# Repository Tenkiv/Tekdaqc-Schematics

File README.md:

# TekdaqcSchematics

pcb file for RevE and RevF are incomplete
- all digital grounds are currently unconnected
#TODO ground plane

RevE contains the files for the current Tekdaqc version

RevF is a modified version of the current Tekdaqc
- GIP15 is moved from PC14 to PH5
- GPI4 is moved from PH0 to PH3
- Digital Output connection has been modified to include a pull down resistor

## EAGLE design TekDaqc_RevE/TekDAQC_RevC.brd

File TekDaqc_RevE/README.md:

Folder contains all necessary files to open and make changes to the schematic and pcb files in KiCad

*.pro - project file

*.sch - schematic files

*.lib - contains the components used in the schematic 

*.kicad_pcb - pcb file

*.pretty - contains the files of the footprints used in the pcb file

*.kicad_mod - footprint of the components used in the pcb file

*.net - links the schematic files to the pcb files

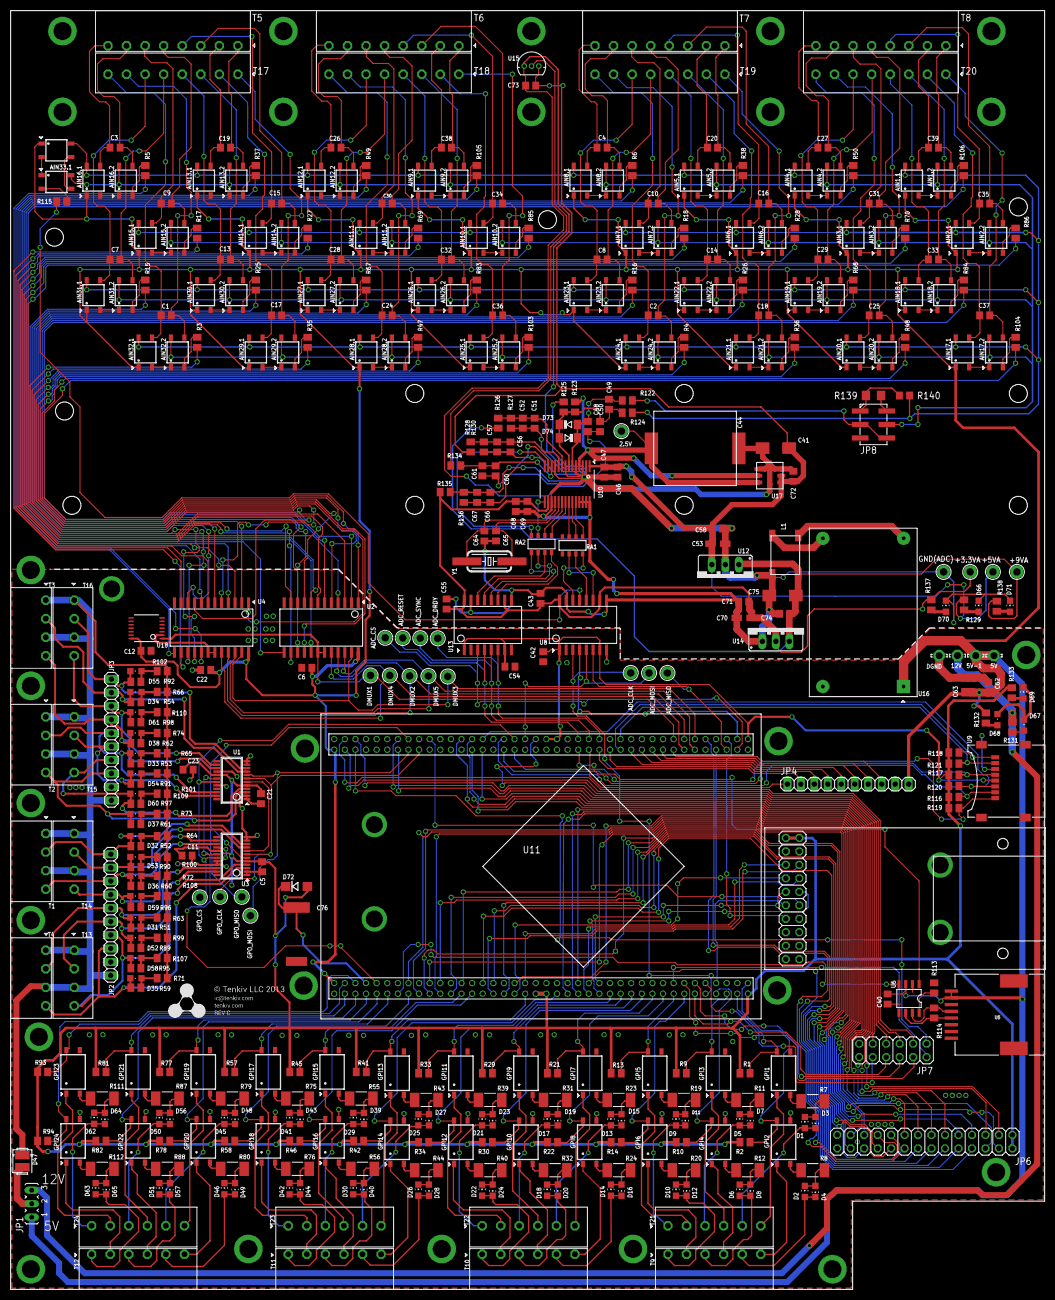
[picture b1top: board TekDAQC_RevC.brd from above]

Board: 2 copper layers, 194.9 x 241.1 mm, 458 parts (0 on the bottom side), 446 nets.

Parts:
2.5V: R; KEYSTONE_5000
5V, 5V-1, 12V: LSP13
+3.3VA, +5VA, +9VA: R; KEYSTONE_5000
ADC_CLK: Y; KEYSTONE_5000
ADC_CS: Y; KEYSTONE_5000
ADC_DRDY: Y; KEYSTONE_5000
ADC_MISO: B; KEYSTONE_5000
ADC_MOSI: W; KEYSTONE_5000
ADC_RESET: W; KEYSTONE_5000
ADC_SYNC: O; KEYSTONE_5000
AIN1.1, AIN1.2, AIN2.1, AIN2.2, AIN3.1, AIN3.2, AIN4.1, AIN4.2, AIN5.1, AIN5.2, AIN6.1, AIN6.2, AIN7.1, AIN7.2, AIN8.1, AIN8.2, AIN9.1, AIN9.2, AIN10.1, AIN10.2, AIN11.1, AIN11.2, AIN12.1, AIN12.2, AIN13.1, AIN13.2, AIN14.1, AIN14.2, AIN15.1, AIN15.2, AIN16.1, AIN16.2, AIN17.1, AIN17.2, AIN18.1, AIN18.2, AIN19.1, AIN19.2, AIN20.1, AIN20.2, AIN21.1, AIN21.2, AIN22.1, AIN22.2, AIN23.1, AIN23.2, AIN24.1, AIN24.2, AIN25.1, AIN25.2, AIN26.1, AIN26.2, AIN27.1, AIN27.2, AIN28.1, AIN28.2, AIN29.1, AIN29.2, AIN30.1, AIN30.2, AIN31.1, AIN31.2, AIN32.1, AIN32.2, AIN33.1, AIN33.2: CPC1025N; SOP4
C1, C2, C3, C4, C5, C6, C7, C8, C9, C10, C11, C12, C13, C14, C15, C16, C17, C18, C19, C20, C21, C22, C23, C24, C25, C26, C27, C28, C29, C30, C31, C32, C33, C34, C35, C36, C37, C38, C39, C40, C42, C43, C46, C49, C52, C54, C55, C57, C58, C61, C62, C67, C68, C71, C72, C73, C74: 0.1uF; C0805
C41, C75: 10uF; CT6032
C44: 4.7uF; 6054
C47, C69: 10uF; C0805
C48, C50: 0.01uF; C0805
C51, C56, C60, C66: 100pF; C0805
C53, C70: 15uF; CT3216
C63: 47uF; C1210
C64, C65: 18pF; C0805
C76: ELNA0_0.33F_CAP; COIN_CELL_CAP
D1, D2, D3, D4, D5, D6, D7, D8, D9, D10, D11, D12, D13, D14, D15, D16, D17, D18, D19, D20, D21, D22, D23, D24, D25, D26, D27, D28, D29, D30, D39, D40, D41, D42, D43, D44, D45, D46, D48, D49, D50, D51, D56, D57, D62, D63, D64, D65: R; CHIP-LED0805
D31, D32, D33, D34, D35, D36, D37, D38, D52, D53, D54, D55, D58, D59, D60, D61: B; CHIPLED_0805
D47: DIODE(DO-214AA); DO−214AA
D66: +5V; CHIP-LED0805
D67: +12V; CHIPLED_0805
D68: +5V; CHIPLED_0805
D69: MCU PWR; CHIP-LED0805
D70: +3.3V; CHIP-LED0805
D71: +9V; CHIP-LED0805
D72: CDBA120LL-G; DO214AC
D73, D74: TZMC5V1-GS08; SOD80C
DGND: LSP13
DMUX1, DMUX2, DMUX3, DMUX4, DMUX5: O; KEYSTONE_5000
DRILEGEND: DRILEGEND
GND(ADC): B; KEYSTONE_5000
GPI1, GPI2, GPI3, GPI4, GPI5, GPI6, GPI7, GPI8, GPI9, GPI10, GPI11, GPI12, GPI13, GPI14, GPI15, GPI16, GPI17, GPI18, GPI19, GPI20, GPI21, GPI22, GPI23, GPI24: 4-SMD
GPO_CLK: Y; KEYSTONE_5000
GPO_CS: Y; KEYSTONE_5000
GPO_MISO: B; KEYSTONE_5000
GPO_MOSI: W; KEYSTONE_5000
JP1: OutputSupply; JP2
JP2: Relay2; 1X10
JP3, JP4: Relay1; 1X10
JP5: ETH Header; ETH_2X10
JP6: Misc Header; 2X14
JP7: PWM Header; 2X06
JP8: 2X3PIN_SMT_HEADER; 2X3SMT_HEADER
L1: BOURNES_DR331-475BE; DR331_CHOKE
R1, R2, R9, R10, R13, R14, R21, R22, R29, R30, R33, R34, R41, R42, R45, R46, R57, R58, R77, R78, R81, R82, R93, R94, R130, R131, R135, R136: 1k; M0805
R3, R4, R5, R6, R15, R16, R17, R18, R25, R26, R27, R28, R35, R36, R37, R38, R47, R48, R49, R50, R63, R64, R65, R66, R67, R68, R69, R70, R71, R72, R73, R74, R83, R84, R85, R86, R99, R100, R101, R102, R103, R104, R105, R106, R107, R108, R109, R110, R115: 442; M0805
R7, R8, R11, R12, R19, R20, R23, R24, R31, R32, R39, R40, R43, R44, R55, R56, R75, R76, R79, R80, R87, R88, R111, R112: 330; R2010
R51, R52, R53, R54, R59, R60, R61, R62, R89, R90, R91, R92, R95, R96, R97, R98, R125: 1M; M0805
R113: 49.9k; M0805
R114: 60; M0805
R116, R117, R118, R119, R120, R121: 10K; M0805
R122, R124, R134: 301; M0805
R123: 0; M0805
R126, R138: 8k; M0805
R127, R128: 2k; M0805
R129, R132, R133, R137: 330; M0805
R139: 1M; R1206
R140: 12.7k; R0805
RA1, RA2: 744C083101JP; 5131(744SERIES)
T1, T2, T3, T4: 4POLE_PLUGIN_TERMINAL_SIDE; 4POLE_3.5MM_TERMINAL_SIDE
T5, T6, T7, T8: 8POLE_PLUGIN_TERMINAL_SIDE; 8POLE_3.5MM_TERMINAL_SIDE
T9, T10, T11, T12: 6POLE_PLUGIN_TERMINAL_SIDE; 6POLE_3.5MM_TERMINAL_SIDE
T13, T14, T15, T16: 4POLE_PLUGIN_TERMINAL_TOP; 4POLE_3.5MM_TERMINAL_TOP
T17, T18, T19, T20: 8POLE_PLUGIN_TERMINAL_TOP; 8POLE_3.5MM_TERMINAL_TOP
T21, T22, T23, T24: 6POLE_PLUGIN_TERMINAL_TOP; 6POLE_3.5MM_TERMINAL_TOP
U1, U3: SPIDER-TLE7232GS; SSOP24
U2, U4: CD74HC154M96; SOIC24
U5: MODULAR_JACK; 44144
U6: MCP2551_SOIC; MCP_SOIC
U8, U13: ISO7241CDW; SOIC16
U9: TF-SD
U10: ADS1256; SSOP28
U11: STM32_CARRIERF407IGT6; STM32_CARRIER
U12: LM7805-T0220; 78XXS
U14: LM1086-3.3; 317TS
U15: LM35; TO-92
U16: VALOR_PM6045; DIL24(4PIN)
U17: LTC6655BHLS8-2.5; CLCC8
U18: 7404MTCX; TSSOP14
U$1: TENKIV_INFO_BLOCK
Y1: HCM49-7.680MABJ-UT; HCM49

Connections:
2.5REF: 2.5V.TP, C44.P$1, R123.2, U10.4, U17.P$6, U17.P$7
+5V: 5V.MP, 5V-1.MP, AIN1.1.1, AIN2.1.1, AIN3.1.1, AIN4.1.1, AIN5.1.1, AIN6.1.1, AIN7.1.1, AIN8.1.1, AIN9.1.1, AIN10.1.1, AIN11.1.1, AIN12.1.1, AIN13.1.1, AIN14.1.1, AIN15.1.1, AIN16.1.1, AIN17.1.1, AIN18.1.1, AIN19.1.1, AIN20.1.1, AIN21.1.1, AIN22.1.1, AIN23.1.1, AIN24.1.1, AIN25.1.1, AIN26.1.1, AIN27.1.1, AIN28.1.1, AIN29.1.1, AIN30.1.1, AIN31.1.1, AIN32.1.1, AIN33.2.1, C6.1, C12.1, C22.1, C40.2, C62.1, C63.1, JP1.1, JP4.10, R132.1, U2.24, U4.24, U5.1, U5.2, U6.3, U11.5V-IN, U11.5V-IN/OUT, U16.1, U18.14
+5V/1: +5VA.TP, C41.+, C46.1, C47.1, C53.+, C58.1, C72.1, C73.1, R128.1, R129.2, U10.1, U12.OUT, U15.1, U17.P$1, U17.P$2
+9V: +9VA.TP, C74.1, C75.+, L1.P$4, R126.1, R138.2, U12.IN, U14.3
+12V: 12V.MP, JP1.3, R131.1
/DMUX4: U4.18, U4.19, U18.2
ADC1_IN0: JP6.4, U11.PA0
ADC1_IN3: JP6.6, U11.PA3
ADC1_IN6: JP6.8, U11.PA6
ADC2_IN10: JP6.10, U11.PC0
ADC2_IN12: JP6.12, U11.PC2
ADC2_IN13: JP6.14, U11.PC3
ADC3_IN4: JP6.16, U11.PF6
ADC3_IN5: JP6.18, U11.PF7
ADC3_IN8: JP6.20, U11.PF10
ADC3_IN9: JP6.22, U11.PF3
ADC3_IN14: JP6.24, U11.PF4
ADC3_IN15: JP6.26, U11.PF5
AIN0: AIN1.2.4, AIN2.2.4, AIN3.2.4, AIN4.2.4, AIN5.2.4, AIN6.2.4, AIN7.2.4, AIN8.2.4, AIN9.2.4, AIN10.2.4, AIN11.2.4, AIN12.2.4, AIN13.2.4, AIN14.2.4, AIN15.2.4, AIN16.2.4, AIN17.2.4, AIN18.2.4, AIN19.2.4, AIN20.2.4, AIN21.2.4, AIN22.2.4, AIN23.2.4, AIN24.2.4, AIN25.2.4, AIN26.2.4, AIN27.2.4, AIN28.2.4, AIN29.2.4, AIN30.2.4, AIN31.2.4, AIN32.2.4, AIN33.1.4, JP8.P$5
AIN1: AIN1.1.4, AIN2.1.4, AIN3.1.4, AIN4.1.4, AIN5.1.4, AIN6.1.4, AIN7.1.4, AIN8.1.4, AIN9.1.4, AIN10.1.4, AIN11.1.4, AIN12.1.4, AIN13.1.4, AIN14.1.4, AIN15.1.4, AIN16.1.4, AIN17.1.4, AIN18.1.4, AIN19.1.4, AIN20.1.4, AIN21.1.4, AIN22.1.4, AIN23.1.4, AIN24.1.4, AIN25.1.4, AIN26.1.4, AIN27.1.4, AIN28.1.4, AIN29.1.4, AIN30.1.4, AIN31.1.4, AIN32.1.4, AIN33.2.4, R124.1, R140.1
CAN1_RX: U6.4, U11.PI9
CAN1_TX: U6.1, U11.PH13
DAC_OUT1: JP6.23, U11.PA4
DAC_OUT2: JP6.25, U11.PA5
DGND: C5.2, C6.2, C11.2, C12.2, C21.2, C22.2, C23.2, C40.1, C42.2, C54.2, C62.2, C63.2, C76.P$2, D67.C, D68.C, D69.C, DGND.MP, GPI1.3, GPI2.3, GPI3.3, GPI4.3, GPI5.3, GPI6.3, GPI7.3, GPI8.3, GPI9.3, GPI10.3, GPI11.3, GPI12.3, GPI13.3, GPI14.3, GPI15.3, GPI16.3, GPI17.3, GPI18.3, GPI19.3, GPI20.3, GPI21.3, GPI22.3, GPI23.3, GPI24.3, JP2.9, JP3.9, JP4.9, JP5.3, JP5.4, JP6.27, JP6.28, JP7.11, JP7.12, R113.2, U1.1, U1.2, U1.11, U1.12, U1.16, U1.20, U1.21, U2.12, U3.1, U3.2, U3.11, U3.12, U3.16, U3.20, U3.21, U4.12, U5.3, U5.6, U5.7, U5.8, U5.G1, U5.G2, U6.2, U8.2, U8.8, U9.G1, U9.G2, U9.G3, U9.G4, U9.PIN6, U11.GND-1, U11.GND-2, U11.GND-3, U11.GND-4, U11.GND-5, U11.GND-6, U11.GND-7, U13.2, U13.8, U16.24, U18.3, U18.5, U18.7, U18.9, U18.11, U18.13
DMUX0: DMUX3.TP, U2.23, U4.23, U11.PD11
DMUX1: DMUX5.TP, U2.22, U4.22, U11.PD12
DMUX2: DMUX2.TP, U2.21, U4.21, U11.PD13
DMUX3: DMUX4.TP, U2.20, U4.20, U11.PD14
DMUX4: DMUX1.TP, U2.18, U2.19, U11.PD15, U18.1
DOUT: RA1.P$6, U8.11
ETH_RMII_CRS_DV: JP5.8, U11.PA7
ETH_RMII_MDC: JP5.6, U11.PC1
ETH_RMII_MDIO: JP5.5, U11.PA2
ETH_RMII_REF_CLK: JP5.7, U11.PA1
ETH_RMII_RXD0: JP5.9, U11.PC4
ETH_RMII_RXD1: JP5.10, U11.PC5
ETH_RMII_TXD0: JP5.12, U11.PG13
ETH_RMII_TXD1: JP5.13, U11.PB13
ETH_RMII_TX_EN: JP5.11, U11.PB11
GND: C41.-, C43.2, C44.P$2, C46.2, C47.2, C48.2, C50.2, C51.2, C52.2, C53.-, C55.2, C56.2, C57.2, C58.2, C60.2, C61.2, C64.2, C65.2, C66.2, C67.2, C68.2, C69.2, C70.-, C71.2, C72.2, C73.2, C74.2, C75.-, D66.C, D70.C, D71.C, GND(ADC).TP, L1.P$3, R125.1, R127.1, R130.1, R136.1, U8.9, U8.15, U10.2, U10.3, U10.5, U10.8, U10.11, U10.17, U10.25, U10.26, U10.27, U10.28, U12.GND, U13.9, U13.15, U14.1, U15.3, U17.P$3, U17.P$4, U17.P$5, U17.P$8
GPI1: GPI24.4, R94.2, U11.PE5
GPI1+: GPI24.1, T12.2
GPI1-: D63.A, D65.C, T12.1
GPI2: GPI22.4, R82.2, U11.PE4
GPI2+: GPI22.1, T12.4
GPI2-: D51.A, D57.C, T12.3
GPI3: GPI20.4, R78.2, U11.PI8
GPI3+: GPI20.1, T12.6
GPI3-: D46.A, D49.C, T12.5
GPI4: GPI18.4, R58.2, U11.PI11
GPI4+: GPI18.1, T11.2
GPI4-: D42.A, D44.C, T11.1
GPI5: GPI16.4, R46.2, U11.PH0
GPI5+: GPI16.1, T11.4
GPI5-: D30.A, D40.C, T11.3
GPI6: GPI14.4, R42.2, U11.PH4
GPI6+: GPI14.1, T11.6
GPI6-: D26.A, D28.C, T11.5
GPI7: GPI12.4, R34.2, U11.PF11
GPI7+: GPI12.1, T10.2
GPI7-: D22.A, D24.C, T10.1
GPI8: GPI10.4, R30.2, U11.PF15
GPI8+: GPI10.1, T10.4
GPI8-: D18.A, D20.C, T10.3
GPI9: GPI8.4, R22.2, U11.PE8
GPI9+: GPI8.1, T10.6
GPI9-: D14.A, D16.C, T10.5
GPI10: GPI6.4, R14.2, U11.PE12
GPI10+: GPI6.1, T9.2
GPI10-: D10.A, D12.C, T9.1
GPI11: GPI4.4, R10.2, U11.PH6
GPI11+: GPI4.1, T9.4
GPI11-: D6.A, D8.C, T9.3
GPI12: GPI2.4, R2.2, U11.PH11
GPI12+: GPI2.1, T9.6
GPI12-: D2.A, D4.C, T9.5
GPI13: GPI23.4, R93.2, U11.PE3
GPI13+: GPI23.1, T24.2
GPI13-: D62.A, D64.C, T24.1
GPI14: GPI21.4, R81.2, U11.PE2
GPI14+: GPI21.1, T24.4
GPI14-: D50.A, D56.C, T24.3
GPI15: GPI19.4, R77.2, U11.PE6
GPI15+: GPI19.1, T24.6
GPI15-: D45.A, D48.C, T24.5
GPI16: GPI17.4, R57.2, U11.PC14
GPI16+: GPI17.1, T23.2
GPI16-: D41.A, D43.C, T23.1
GPI17: GPI15.4, R45.2, U11.PF9
GPI17+: GPI15.1, T23.4
GPI17-: D29.A, D39.C, T23.3
GPI18: GPI13.4, R41.2, U11.PH2
GPI18+: GPI13.1, T23.6
GPI18-: D25.A, D27.C, T23.5
GPI19: GPI11.4, R33.2, U11.PB1
GPI19+: GPI11.1, T22.2
GPI19-: D21.A, D23.C, T22.1
GPI20: GPI9.4, R29.2, U11.PF13
GPI20+: GPI9.1, T22.4
GPI20-: D17.A, D19.C, T22.3
GPI21: GPI7.4, R21.2, U11.PG1
GPI21+: GPI7.1, T22.6
GPI21-: D13.A, D15.C, T22.5
GPI22: GPI5.4, R13.2, U11.PE10
GPI22+: GPI5.1, T21.2
GPI22-: D9.A, D11.C, T21.1
GPI23: GPI3.4, R9.2, U11.PH8
GPI23+: GPI3.1, T21.4
GPI23-: D5.A, D7.C, T21.3
GPI24: GPI1.4, R1.2, U11.PH10
GPI24+: GPI1.1, T21.6
GPI24-: D1.A, D3.C, T21.5
I2C1_SCL: JP6.3, U11.PB6
I2C1_SDA: JP6.5, U11.PB7
I2C2_SCL: JP6.7, U11.PF1
I2C2_SDA: JP6.9, U11.PF0
unnamed: D68.A, R132.2
unnamed: AIN33.1.2, R115.2
unnamed: RA2.P$3, U10.15
unnamed: D67.A, R131.2
unnamed: AIN33.1.1, AIN33.2.2
unnamed: R134.1, U15.2
unnamed: C48.1, C49.1, D73.A, D74.C, R122.2, U10.6
unnamed: C49.2, C50.1, D73.C, D74.A, R123.1, R124.2, R125.2, U10.7
unnamed: D69.A, R133.1
unnamed: AIN1.2.2, R106.2
unnamed: AIN2.2.2, R86.2
unnamed: C65.1, U10.19, Y1.P$1
unnamed: C64.1, U10.18, Y1.P$2
unnamed: AIN1.1.2, AIN1.2.1
unnamed: RA1.P$2, U10.23
unnamed: RA1.P$1, U10.24
unnamed: D70.A, R137.1
unnamed: RA1.P$8, U8.14
unnamed: RA1.P$7, U8.12
unnamed: AIN25.1.2, AIN25.2.1
unnamed: AIN25.2.2, R103.2
unnamed: AIN2.1.2, AIN2.2.1
unnamed: AIN3.1.2, AIN3.2.1
unnamed: AIN3.2.2, R70.2
unnamed: AIN4.2.2, R50.2
unnamed: AIN4.1.2, AIN4.2.1
unnamed: AIN5.1.2, AIN5.2.1
unnamed: AIN5.2.2, R38.2
unnamed: AIN6.2.2, R28.2
unnamed: AIN7.2.2, R18.2
unnamed: AIN6.1.2, AIN6.2.1
unnamed: AIN7.1.2, AIN7.2.1
unnamed: AIN8.1.2, AIN8.2.1
unnamed: AIN8.2.2, R6.2
unnamed: AIN9.2.2, R105.2
unnamed: AIN9.1.2, AIN9.2.1
unnamed: AIN10.1.2, AIN10.2.1
unnamed: AIN10.2.2, R85.2
unnamed: AIN11.2.2, R69.2
unnamed: AIN11.1.2, AIN11.2.1
unnamed: AIN12.1.2, AIN12.2.1
unnamed: AIN12.2.2, R49.2
unnamed: AIN13.1.2, AIN13.2.1
unnamed: AIN13.2.2, R37.2
unnamed: AIN14.1.2, AIN14.2.1
unnamed: AIN14.2.2, R27.2
unnamed: AIN15.1.2, AIN15.2.1
unnamed: AIN15.2.2, R17.2
unnamed: AIN16.1.2, AIN16.2.1
unnamed: AIN16.2.2, R5.2
unnamed: AIN26.2.2, R83.2
unnamed: AIN26.1.2, AIN26.2.1
unnamed: AIN27.1.2, AIN27.2.1
unnamed: AIN27.2.2, R67.2
unnamed: AIN28.1.2, AIN28.2.1
unnamed: AIN28.2.2, R47.2
unnamed: AIN29.1.2, AIN29.2.1
unnamed: AIN29.2.2, R35.2
unnamed: AIN30.1.2, AIN30.2.1
unnamed: AIN30.2.2, R25.2
unnamed: AIN31.1.2, AIN31.2.1
unnamed: AIN31.2.2, R15.2
unnamed: AIN32.1.2, AIN32.2.1
unnamed: AIN32.2.2, R3.2
unnamed: D47.2, JP2.10, JP3.10, R63.1, R64.1, R65.1, R66.1, R71.1, R72.1, R73.1, R74.1, R99.1, R100.1, R101.1, R102.1, R107.1, R108.1, R109.1, R110.1, T1.1, T1.3, T2.1, T2.3, T3.1, T3.3, T4.1, T4.3, T13.1, T13.3, T14.1, T14.3, T15.1, T15.3, T16.1, T16.3
unnamed: AIN17.2.2, R104.2
unnamed: AIN18.2.2, R84.2
unnamed: AIN19.2.2, R68.2
unnamed: AIN20.2.2, R48.2
unnamed: U1.6, U3.8
unnamed: AIN21.2.2, R36.2
unnamed: AIN22.2.2, R26.2
unnamed: AIN23.2.2, R16.2
unnamed: AIN24.2.2, R4.2
unnamed: AIN17.1.2, AIN17.2.1
unnamed: AIN18.1.2, AIN18.2.1
unnamed: AIN19.1.2, AIN19.2.1
unnamed: AIN20.1.2, AIN20.2.1
unnamed: AIN21.1.2, AIN21.2.1
unnamed: AIN22.1.2, AIN22.2.1
unnamed: AIN23.1.2, AIN23.2.1
unnamed: AIN24.1.2, AIN24.2.1
unnamed: D31.A, R51.1, R63.2
unnamed: D35.A, R59.1, R71.2
unnamed: R114.2, U5.4, U6.7
unnamed: R114.1, U5.5, U6.6
unnamed: R113.1, U6.8
unnamed: RA2.P$2, U10.20
unnamed: D34.A, R54.1, R66.2
unnamed: AIN33.1.3, AIN33.2.3
unnamed: R115.1, U8.13
unnamed: L1.P$1, U16.12
unnamed: JP8.P$2, JP8.P$4, R122.1
unnamed: L1.P$2, U16.13
unnamed: D47.1, JP1.2
unnamed: D38.A, R62.1, R74.2
unnamed: D33.A, R53.1, R65.2
unnamed: D37.A, R61.1, R73.2
unnamed: D32.A, R52.1, R64.2
unnamed: D36.A, R60.1, R72.2
unnamed: JP8.P$6, R139.2
unnamed: JP8.P$1, R139.1, R140.2
unnamed: D55.A, R92.1, R102.2
unnamed: D61.A, R98.1, R110.2
unnamed: D54.A, R91.1, R101.2
unnamed: D60.A, R97.1, R109.2
unnamed: D53.A, R90.1, R100.2
unnamed: D59.A, R96.1, R108.2
unnamed: D52.A, R89.1, R99.2
unnamed: D58.A, R95.1, R107.2
unnamed: RA2.P$1, U10.21
unnamed: RA2.P$4, U10.14
unnamed: RA2.P$8, U13.11
unnamed: RA2.P$5, U13.12
unnamed: RA2.P$6, U13.13
unnamed: RA2.P$7, U13.14
unnamed: C51.1, C52.1, R126.2, R127.2, U10.9
unnamed: RA1.P$3, U10.22
unnamed: D71.A, R138.1
unnamed: D66.A, R129.1
unnamed: C66.1, C67.1, R135.2, R136.2, U10.13
unnamed: C60.1, C61.1, R134.2, U10.12
unnamed: C56.1, C57.1, R128.2, R130.2, U10.10
unnamed: GPI22.2, R88.2
unnamed: GPI20.2, R80.2
unnamed: GPI18.2, R76.2
unnamed: GPI16.2, R56.2
unnamed: GPI14.2, R44.2
unnamed: GPI12.2, R40.2
unnamed: GPI10.2, R32.2
unnamed: GPI8.2, R24.2
unnamed: GPI6.2, R20.2
unnamed: GPI4.2, R12.2
unnamed: GPI2.2, R8.2
unnamed: GPI23.2, R111.2
unnamed: GPI21.2, R87.2
unnamed: GPI19.2, R79.2
unnamed: GPI17.2, R75.2
unnamed: GPI15.2, R55.2
unnamed: GPI13.2, R43.2
unnamed: GPI11.2, R39.2
unnamed: GPI9.2, R31.2
unnamed: GPI7.2, R23.2
unnamed: GPI5.2, R19.2
unnamed: GPI3.2, R11.2
unnamed: GPI1.2, R7.2
unnamed: GPI24.2, R112.2
unnamed: D63.C, D65.A, R112.1
unnamed: D51.C, D57.A, R88.1
unnamed: D46.C, D49.A, R80.1
unnamed: D42.C, D44.A, R76.1
unnamed: D30.C, D40.A, R56.1
unnamed: D26.C, D28.A, R44.1
unnamed: D22.C, D24.A, R40.1
unnamed: D18.C, D20.A, R32.1
unnamed: D14.C, D16.A, R24.1
unnamed: D10.C, D12.A, R20.1
unnamed: D6.C, D8.A, R12.1
unnamed: D2.C, D4.A, R8.1
unnamed: D62.C, D64.A, R111.1
unnamed: D50.C, D56.A, R87.1
unnamed: D45.C, D48.A, R79.1
unnamed: D41.C, D43.A, R75.1
unnamed: D29.C, D39.A, R55.1
unnamed: D25.C, D27.A, R43.1
unnamed: D21.C, D23.A, R39.1
unnamed: D17.C, D19.A, R31.1
unnamed: D13.C, D15.A, R23.1
unnamed: D9.C, D11.A, R19.1
unnamed: D5.C, D7.A, R11.1
unnamed: D1.C, D3.A, R7.1
OCAL: U8.4, U11.PH12
REL1_IN1: JP4.8, U11.PG2
REL1_IN2: JP4.7, U11.PG4
REL1_IN3: JP4.6, U11.PG6
REL1_IN4: JP4.5, U11.PG8
REL1_IN5: JP4.4, U11.PC7
REL1_IN6: JP4.3, U11.PA9
REL1_IN7: JP4.2, U11.PA11
REL1_IN8: JP4.1, U11.PA13
SDIO_CLK: R117.1, U9.PIN5, U11.PC12
SDIO_CMD: R120.1, U9.PIN3, U11.PD2
SDIO_D0: R121.1, U9.PIN7, U11.PC8
SDIO_D1: R118.1, U9.PIN8, U11.PC9
SDIO_D2: R119.1, U9.PIN1, U11.PC10
SDIO_D3: R116.1, U9.PIN2, U11.PC11
SENS1: R106.1, U2.4
SENS2: R86.1, U2.3
SENS3: R70.1, U2.7
SENS4: R50.1, U2.8
SENS5: R38.1, U2.17
SENS6: R28.1, U2.11
SENS7: R18.1, U2.14
SENS8: R6.1, U2.13
SENS9: R105.1, U4.4
SENS10: R85.1, U4.3
SENS11: R69.1, U4.7
SENS12: R49.1, U4.8
SENS13: R37.1, U4.17
SENS14: R27.1, U4.11
SENS15: R17.1, U4.14
SENS16: R5.1, U4.13
SENS17: R104.1, U2.1
SENS18: R84.1, U2.2
SENS19: R68.1, U2.6
SENS20: R48.1, U2.5
SENS21: R36.1, U2.9
SENS22: R26.1, U2.10
SENS23: R16.1, U2.15
SENS24: R4.1, U2.16
SENS25: R103.1, U4.1
SENS26: R83.1, U4.2
SENS27: R67.1, U4.6
SENS28: R47.1, U4.5
SENS29: R35.1, U4.9
SENS30: R25.1, U4.10
SENS31: R15.1, U4.15
SENS32: R3.1, U4.16
SPI1_MISO: GPO_MISO.TP, U3.6, U11.PB4
SPI1_MOSI: GPO_MOSI.TP, U1.8, U11.PB5
SPI1_NSS: GPO_CS.TP, U1.19, U3.19, U11.PA15
SPI1_SCK: GPO_CLK.TP, U1.7, U3.7, U11.PB3
SPI2_DRDY: ADC_DRDY.TP, U11.PA10, U13.6
SPI2_MISO: ADC_MISO.TP, U8.6, U11.PB14
SPI2_MOSI: ADC_MOSI.TP, U8.5, U11.PI3
SPI2_NSS: ADC_CS.TP, U11.PB12, U13.3
SPI2_RST: ADC_RESET.TP, U11.PH14, U13.4
SPI2_SCK: ADC_CLK.TP, U8.3, U11.PB10
SPI2_SYNC: ADC_SYNC.TP, U11.PA12, U13.5
SPIDER_RST: U1.18, U3.18, U11.PC13
T1.1: AIN1.2.3, C39.1, T8.1
T1.2: AIN1.1.3, C39.2, T8.2
T1.3: AIN2.2.3, C35.1, T8.3
T1.4: AIN2.1.3, C35.2, T8.4
T1.5: AIN3.2.3, C31.1, T8.5
T1.6: AIN3.1.3, C31.2, T8.6
T1.7: AIN4.2.3, C27.1, T8.7
T1.8: AIN4.1.3, C27.2, T8.8
T2.1: AIN5.2.3, C20.1, T7.1
T2.2: AIN5.1.3, C20.2, T7.2
T2.3: AIN6.2.3, C16.1, T7.3
T2.4: AIN6.1.3, C16.2, T7.4
T2.5: AIN7.2.3, C10.1, T7.5
T2.6: AIN7.1.3, C10.2, T7.6
T2.7: AIN8.2.3, C4.1, T7.7
T2.8: AIN8.1.3, C4.2, T7.8
T3.1: AIN9.2.3, C38.1, T6.1
T3.2: AIN9.1.3, C38.2, T6.2
T3.3: AIN10.2.3, C34.1, T6.3
T3.4: AIN10.1.3, C34.2, T6.4
T3.5: AIN11.2.3, C30.1, T6.5
T3.6: AIN11.1.3, C30.2, T6.6
T3.7: AIN12.2.3, C26.1, T6.7
T3.8: AIN12.1.3, C26.2, T6.8
T4.1: AIN13.2.3, C19.1, T5.1
T4.2: AIN13.1.3, C19.2, T5.2
T4.3: AIN14.2.3, C15.1, T5.3
T4.4: AIN14.1.3, C15.2, T5.4
T4.5: AIN15.2.3, C9.1, T5.5
T4.6: AIN15.1.3, C9.2, T5.6
T4.7: AIN16.2.3, C3.1, T5.7
T4.8: AIN16.1.3, C3.2, T5.8
T5.1: AIN17.2.3, C37.1, T20.1
T5.2: AIN17.1.3, C37.2, T20.2
T5.3: AIN18.2.3, C33.1, T20.3
T5.4: AIN18.1.3, C33.2, T20.4
T5.5: AIN19.2.3, C29.1, T20.5
T5.6: AIN19.1.3, C29.2, T20.6
T5.7: AIN20.2.3, C25.1, T20.7
T5.8: AIN20.1.3, C25.2, T20.8
T6.1: AIN21.2.3, C18.1, T19.1
T6.2: AIN21.1.3, C18.2, T19.2
T6.3: AIN22.2.3, C14.1, T19.3
T6.4: AIN22.1.3, C14.2, T19.4
T6.5: AIN23.2.3, C8.1, T19.5
T6.6: AIN23.1.3, C8.2, T19.6
T6.7: AIN24.2.3, C2.1, T19.7
T6.8: AIN24.1.3, C2.2, T19.8
T7.1: AIN25.2.3, C36.1, T18.1
T7.2: AIN25.1.3, C36.2, T18.2
T7.3: AIN26.2.3, C32.1, T18.3
T7.4: AIN26.1.3, C32.2, T18.4
T7.5: AIN27.2.3, C28.1, T18.5
T7.6: AIN27.1.3, C28.2, T18.6
T7.7: AIN28.2.3, C24.1, T18.7
T7.8: AIN28.1.3, C24.2, T18.8
T8.1: AIN29.2.3, C17.1, T17.1
T8.2: AIN29.1.3, C17.2, T17.2
T8.3: AIN30.2.3, C13.1, T17.3
T8.4: AIN30.1.3, C13.2, T17.4
T8.5: AIN31.2.3, C7.1, T17.5
T8.6: AIN31.1.3, C7.2, T17.6
T8.7: AIN32.2.3, C1.1, T17.7
T8.8: AIN32.1.3, C1.2, T17.8
T9.2: D34.C, JP3.2, R54.2, T3.2, U1.9
T9.4: D38.C, JP3.4, R62.2, T3.4, U1.15
T10.2: D33.C, JP3.5, R53.2, T2.2, U1.22
T10.4: D37.C, JP3.8, R61.2, T2.4, U1.3
T11.2: D32.C, JP2.1, R52.2, T1.2, U3.10
T11.4: D36.C, JP2.3, R60.2, T1.4, U3.14
T12.2: D31.C, JP2.5, R51.2, T4.2, U3.22
T12.4: D35.C, JP2.8, R59.2, T4.4, U3.3
T13.2: D55.C, JP3.1, R92.2, T16.2, U1.10
T13.4: D61.C, JP3.3, R98.2, T16.4, U1.14
T14.2: D54.C, JP3.6, R91.2, T15.2, U1.23
T14.4: D60.C, JP3.7, R97.2, T15.4, U1.4
T15.2: D53.C, JP2.2, R90.2, T14.2, U3.9
T15.4: D59.C, JP2.4, R96.2, T14.4, U3.15
T16.2: D52.C, JP2.6, R89.2, T13.2, U3.23
T16.4: D58.C, JP2.7, R95.2, T13.4, U3.4
TIM1_BKIN: JP7.10, U11.PE15
TIM1_CH1: JP7.2, U11.PE9
TIM1_CH2: JP7.4, U11.PE11
TIM1_CH3: JP7.6, U11.PE13
TIM1_CH4: JP7.8, U11.PE14
TIM8_BKIN: JP7.9, U11.PI4
TIM8_CH1: JP7.1, U11.PI5
TIM8_CH2: JP7.3, U11.PI6
TIM8_CH3: JP7.5, U11.PI7
TIM8_CH4: JP7.7, U11.PI2
USART2_CTS: JP6.11, U11.PD3
USART2_RTS: JP6.13, U11.PD4
USART2_RX: JP6.15, U11.PD6
USART2_TX: JP6.17, U11.PD5
USART3_RX: JP6.19, U11.PD9
USART3_TX: JP6.21, U11.PD8
VBAT: C76.P$1, D72.C, U11.VBAT
VCC: C5.1, C11.1, C21.1, C23.1, C42.1, C54.1, D72.A, JP5.1, JP5.2, JP6.1, JP6.2, R1.1, R2.1, R9.1, R10.1, R13.1, R14.1, R21.1, R22.1, R29.1, R30.1, R33.1, R34.1, R41.1, R42.1, R45.1, R46.1, R57.1, R58.1, R77.1, R78.1, R81.1, R82.1, R93.1, R94.1, R116.2, R117.2, R118.2, R119.2, R120.2, R121.2, R133.2, U1.5, U1.17, U3.5, U3.17, U8.1, U8.7, U9.PIN4, U11.3.3V-1, U11.3.3V-2, U11.3.3V-3, U11.3.3V-4, U11.3.3V-5, U11.3.3V-6, U13.1, U13.7
VDD: +3.3VA.TP, C43.1, C55.1, C68.1, C69.1, C70.+, C71.1, R135.1, R137.2, U8.10, U8.16, U10.16, U13.10, U13.16, U14.2

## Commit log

2018-03-20 Init Repo
2018-03-22 Create emptyFile
2018-03-22 schematic/pcb/library files
    schematic files - '*.sch'
    pcb file - '*.brd'
    library - '*.lib'
    net - '*.net'
2018-03-22 Footprints used on pcb board
2018-03-22 renamed: TekDaqc_RevE/TekDAQC_RevE.pretty/TekDAQC_RevE.pretty/7404MTCX_TSSOP14.kicad_mod -> TekDaqc_RevE/TekDAQC_RevE.pretty/7404MTCX_TSSOP14.kicad_mod renamed: TekDaqc_RevE/TekDAQC_RevE.pretty/TekDA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
2018-03-22 general file explanation
2018-05-02 **Notes**
2018-05-06 current tekdaqc unmodified
2018-05-06 new file: TekDAQC_RevF/TekDAQC_RevF.kicad_pcb new file: TekDAQC_RevF/TekDAQC_RevF.lib new file: TekDAQC_RevF/TekDAQC_RevF.net new file: TekDAQC_RevF/TekDAQC_RevF.pretty/7404MTCX_TSSOP14.kicad_mod new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
2018-05-06 added a readme for RevF
2018-08-13 Add LICENSE
